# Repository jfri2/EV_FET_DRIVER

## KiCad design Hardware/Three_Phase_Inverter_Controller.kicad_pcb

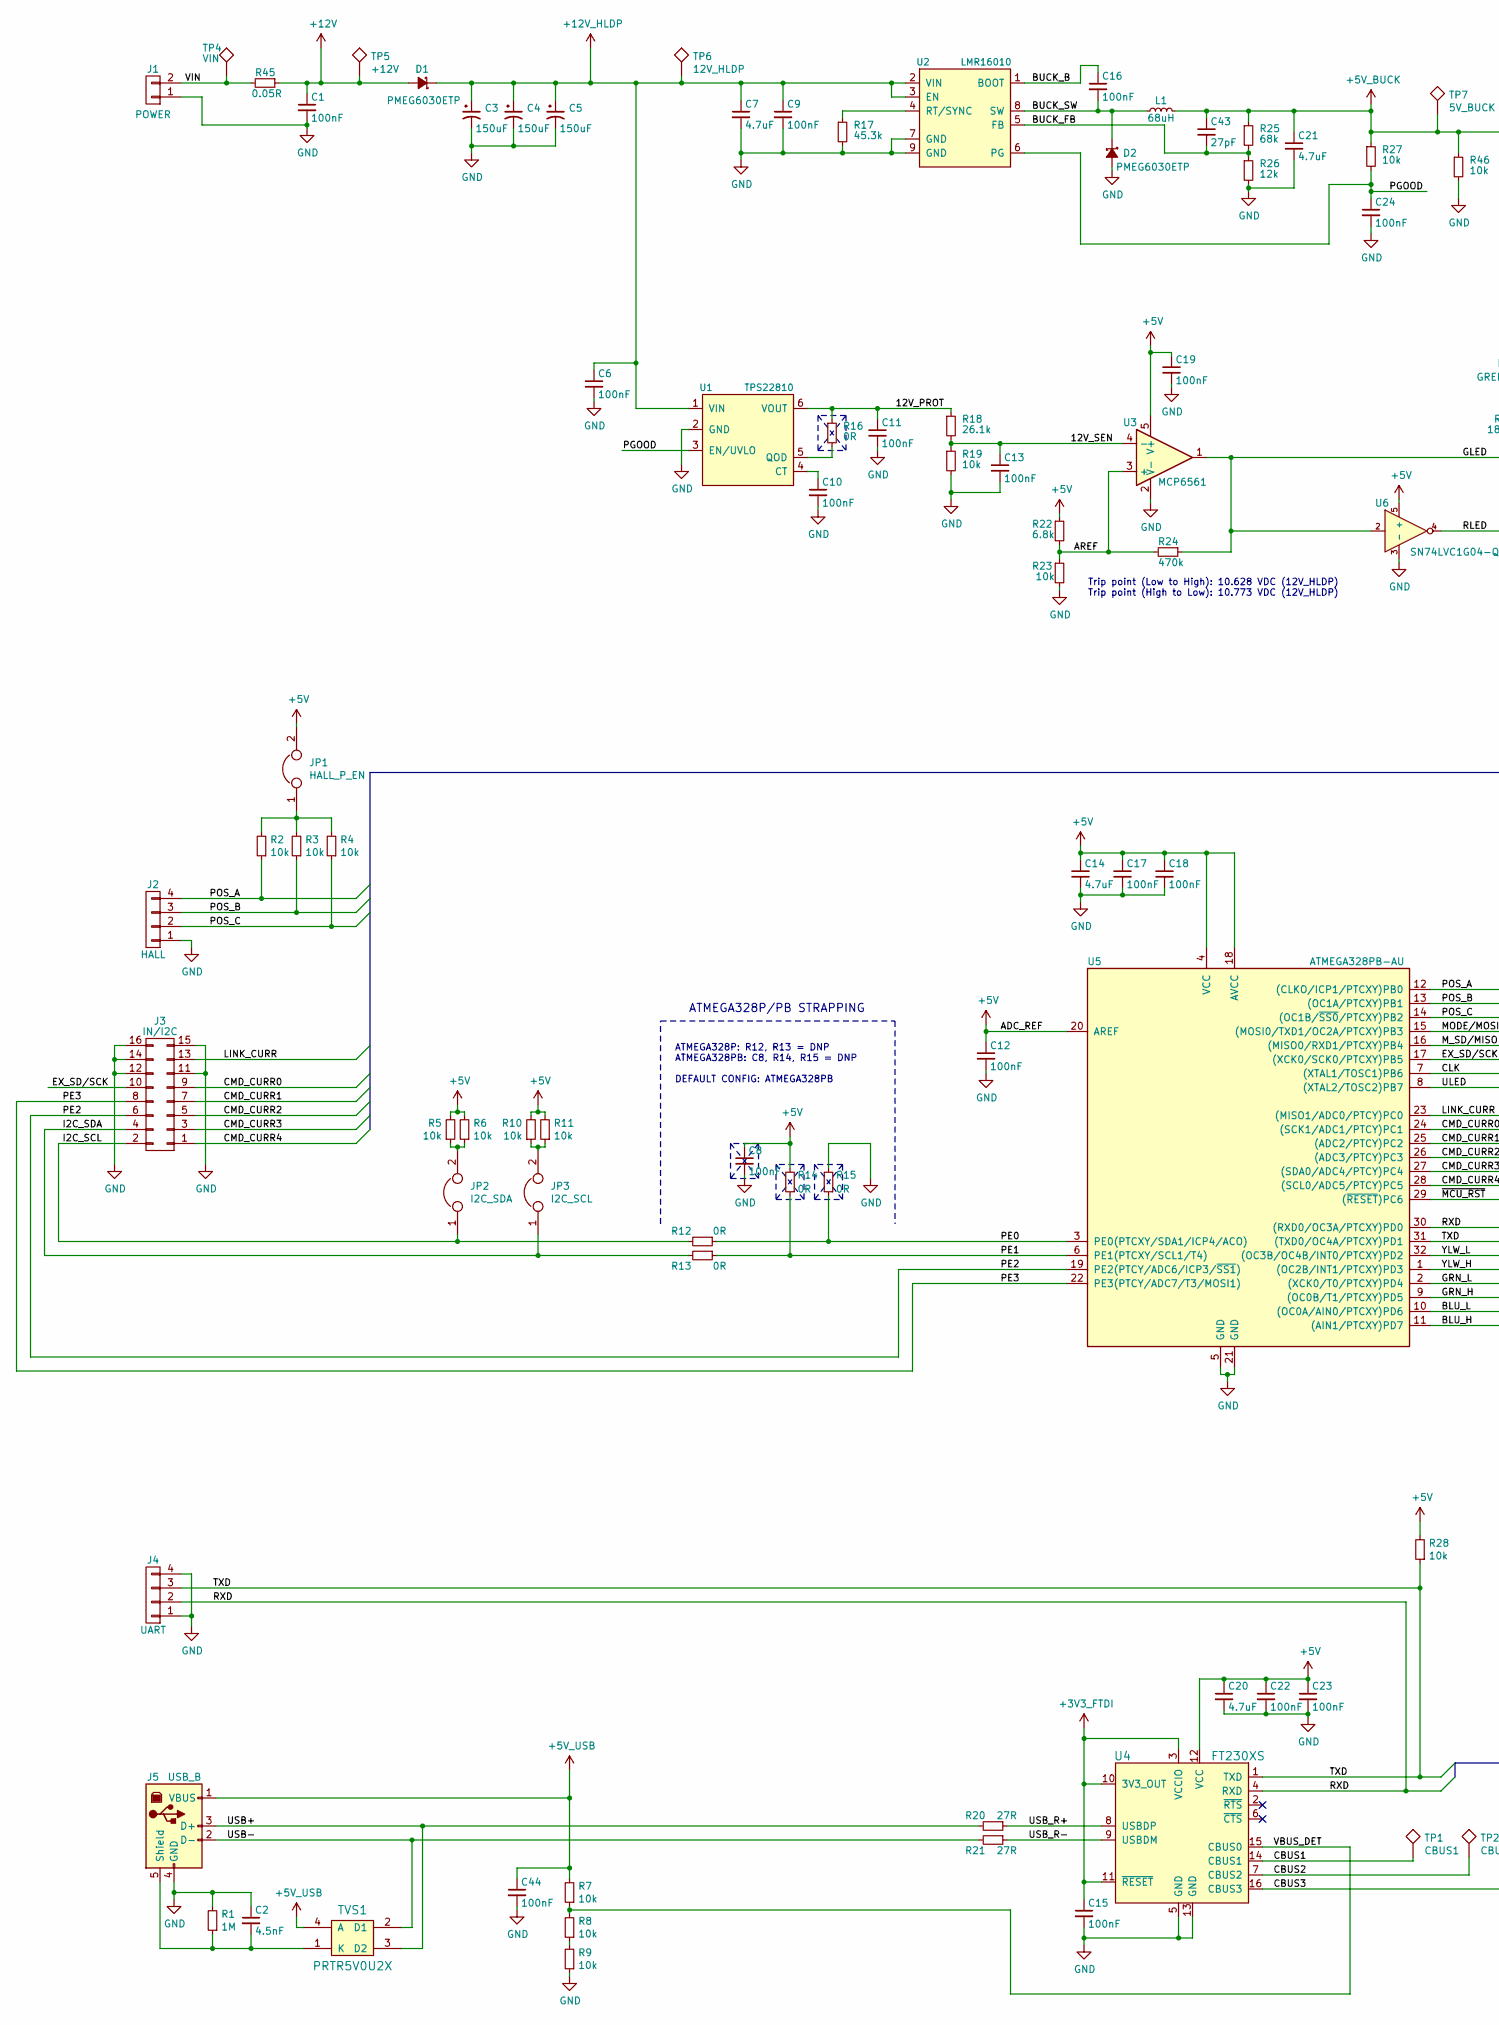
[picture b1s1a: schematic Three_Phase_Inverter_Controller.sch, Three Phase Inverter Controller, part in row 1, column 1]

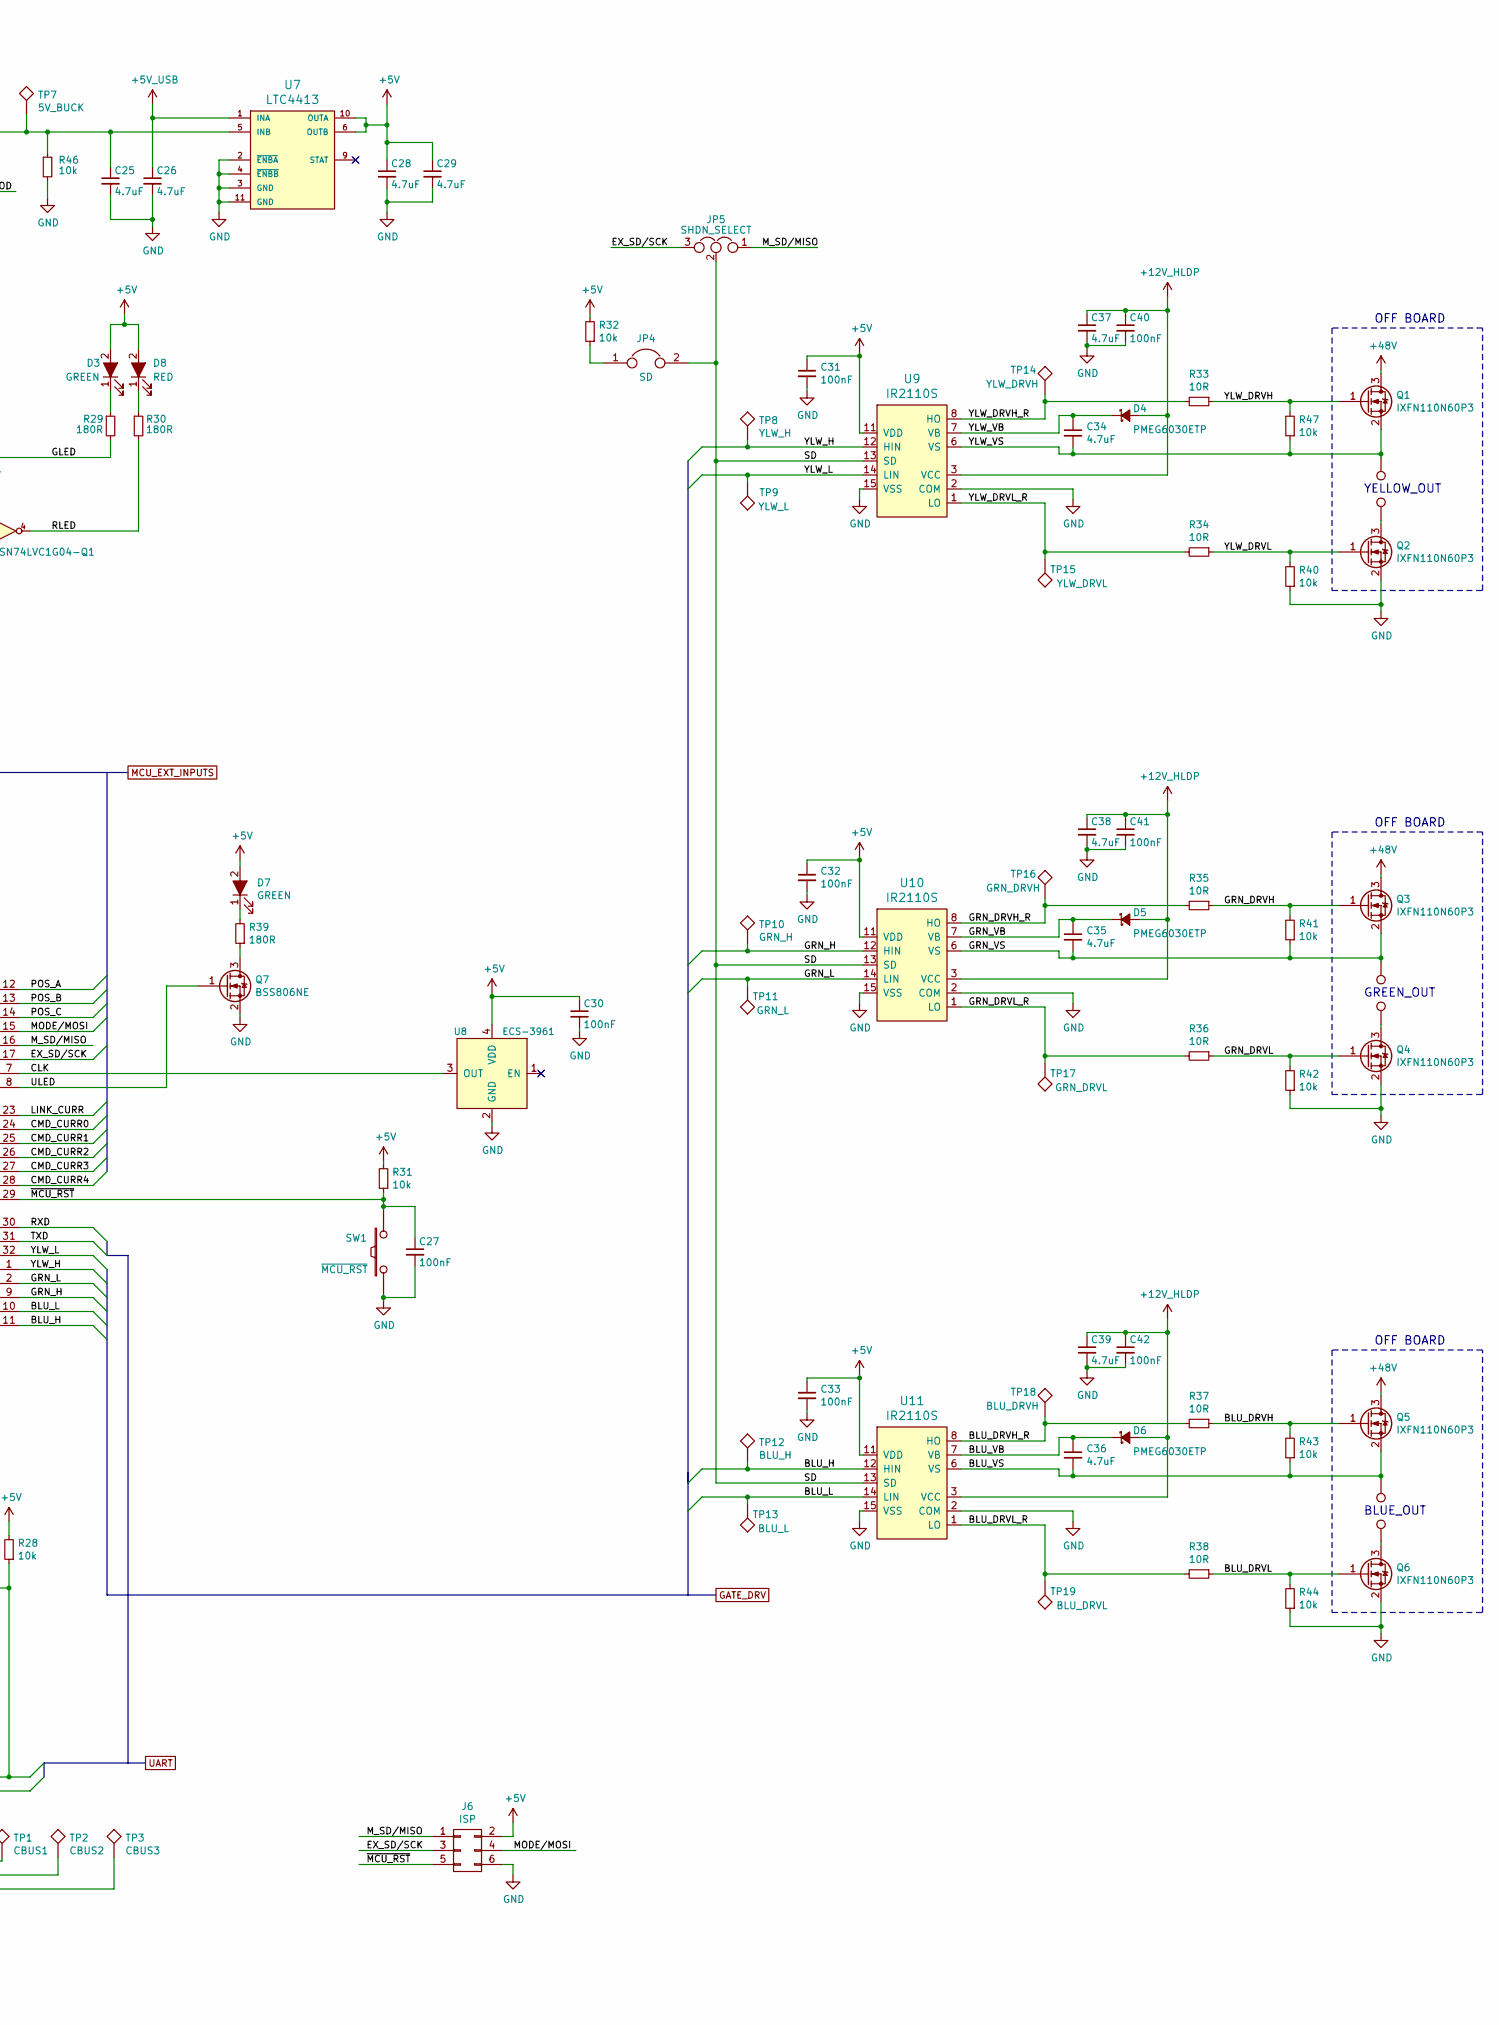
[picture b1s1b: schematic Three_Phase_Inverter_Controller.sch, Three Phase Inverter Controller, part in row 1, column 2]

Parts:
AA1, AA3, AA5: OUT_1_H
AA2, AA4, AA6: OUT_1_L
C1, C6, C8, C9, C10, C11, C12, C13, C15, C16, C17, C18, C19, C22, C23, C24, C27, C30, C31, C32, C33, C40, C41, C42, C44: 100nF; C_0603
C2: 4.5nF; C_0603
C3, C4, C5: 150uF; CP_Elec_10x10.5
C7, C14, C20, C21, C25, C26, C28, C29, C34, C35, C36, C37, C38, C39: 4.7uF; C_1206
C43: 27pF; C_0603
D1, D2, D4, D5, D6: PMEG6030ETP; SOD-128
D3, D7: GREEN; LED_1206
D8: RED; LED_1206
J1: POWER; TerminalBlock_Pheonix_MPT-2.54mm_2pol
J2: HALL; TerminalBlock_Pheonix_MPT-2.54mm_4pol
J3: IN/I2C; Pin_Header_Angled_2x08_Pitch2.54mm
J4: UART; Pin_Header_Angled_1x04_Pitch2.54mm
J5: USB_B; USB-B_62910416121
J6: ISP; Pin_Header_Straight_2x03_Pitch2.54mm
JP1: HALL_P_EN; Pin_Header_Straight_2x01_Pitch2.00mm
JP2: I2C_SDA; Pin_Header_Straight_2x01_Pitch2.00mm
JP3: I2C_SCL; Pin_Header_Straight_2x01_Pitch2.00mm
JP4: SD; Pin_Header_Straight_2x01_Pitch2.00mm
JP5: SHDN_SELECT; Pin_Header_Straight_1x03_Pitch2.54mm
L1: 68uH; BOURNS_SDR0604
Q1, Q2, Q3, Q4, Q5, Q6: IXFN110N60P3; M4_SCREW_OFFSET_9.5_16ths
Q7: BSS806NE; SOT-23
R1: 1M; R_0603
R2, R3, R4, R5, R6, R7, R8, R9, R10, R11, R19, R23, R27, R28, R31, R32, R40, R41, R42, R43, R44, R46, R47: 10k; R_0603
R12, R13, R14, R15, R16: 0R; R_0603
R17: 45.3k; R_0603
R18: 26.1k; R_0603
R20, R21: 27R; R_0603
R22: 6.8k; R_0603
R24: 470k; R_0603
R25: 68k; R_0603
R26: 12k; R_0603
R29, R30: 180R; R_0805
R33, R34, R35, R36, R37, R38: 10R; R_0805
R39: 180R; R_0603
R45: 0.05R; R_1206
SW1: ~MCU_RST; SW_SPST_TL3342
TP1: CBUS1; Test_Point_Keystone_5019_Minature
TP2: CBUS2; Test_Point_Keystone_5019_Minature
TP3: CBUS3; Test_Point_Keystone_5019_Minature
TP4: VIN; Test_Point_Keystone_5019_Minature
TP5: +12V; Test_Point_Keystone_5019_Minature
TP6: 12V_HLDP; Test_Point_Keystone_5019_Minature
TP7: 5V_BUCK; Test_Point_Keystone_5019_Minature
TP8: YLW_H; Test_Point_Keystone_5019_Minature
TP9: YLW_L; Test_Point_Keystone_5019_Minature
TP10: GRN_H; Test_Point_Keystone_5019_Minature
TP11: GRN_L; Test_Point_Keystone_5019_Minature
TP12: BLU_H; Test_Point_Keystone_5019_Minature
TP13: BLU_L; Test_Point_Keystone_5019_Minature
TP14: YLW_DRVH; Test_Point_Keystone_5019_Minature
TP15: YLW_DRVL; Test_Point_Keystone_5019_Minature
TP16: GRN_DRVH; Test_Point_Keystone_5019_Minature
TP17: GRN_DRVL; Test_Point_Keystone_5019_Minature
TP18: BLU_DRVH; Test_Point_Keystone_5019_Minature
TP19: BLU_DRVL; Test_Point_Keystone_5019_Minature
TVS1: PRTR5V0U2X; SOT-143
U1: TPS22810; SOT-23-6
U2: LMR16010; SOIC-8-1EP_3.9x4.9mm_Pitch1.27mm
U3: MCP6561; SOT-23-5
U4: FT230XS; SSOP-16_3.9x4.9mm_Pitch0.635mm
U5: ATMEGA328PB-AU; TQFP-32_7x7mm_Pitch0.8mm
U6: SN74LVC1G04-Q1; SOT-23-5
U7: LTC4413; DFN-10-1EP_3x3mm_Pitch0.5mm
U8: ECS-3961; Oscillator_SMD_EuroQuartz_XO53-4pin_5.0x3.2mm
U9, U10, U11: IR2110S; SOIC-16W_7.5x10.3mm_Pitch1.27mm

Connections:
+3V3_FTDI: C15.1, U4.3 (VCCIO), U4.10 (3V3_OUT), U4.11 (~RESET)
+5V: C8.1, C12.1, C14.1, C17.1, C18.1, C19.1, C20.1, C22.1, C23.1, C28.1, C29.1, C30.1, C31.1, C32.1, C33.1, D3.2 (A), D7.2 (A), D8.2 (A), J6.2, JP1.2, R5.2, R6.2, R10.2, R11.2, R14.2, R22.1, R28.2, R31.2, R32.2, U3.5 (V+), U4.12 (VCC), U5.4 (VCC), U5.18 (AVCC), U5.20 (AREF), U6.5 (+), U7.6 (OUTB), U7.10 (OUTA), U8.4 (VDD), U9.11 (VDD), U10.11 (VDD), U11.11 (VDD)
+5V_BUCK: C21.1, C25.1, C43.1, L1.2, R25.1, R27.1, R46.1, TP7.1, U7.5 (INB)
+5V_USB: C26.1, C44.1, J5.1 (VBUS), R7.2, TVS1.4 (A), U7.1 (INA)
+12V: C1.1, D1.2 (A), R45.1, TP5.1
+12V_HLDP: C3.1, C4.1, C5.1, C6.1, C7.1, C9.1, C37.1, C38.1, C39.1, C40.1, C41.1, C42.1, D1.1 (K), D4.2 (A), D5.2 (A), D6.2 (A), TP6.1, U1.1 (VIN), U2.2 (VIN), U2.3 (EN), U9.3 (VCC), U10.3 (VCC), U11.3 (VCC)
/12V_PROT: C11.1, R16.1, R18.1, U1.6 (VOUT)
/12V_SEN: C13.1, R18.2, R19.1, U3.4 (-)
/AREF: R22.2, R23.1, R24.2, U3.3 (+)
/BLU_DRVH: Q5.1 (G), R37.1, R43.2
/BLU_DRVH_R: R37.2, TP18.1, U11.8 (HO)
/BLU_DRVL: Q6.1 (G), R38.1, R44.2
/BLU_DRVL_R: R38.2, TP19.1, U11.1 (LO)
/BLU_H: TP12.1, U5.11 ((AIN1/PTCXY)PD7), U11.12 (HIN)
/BLU_L: TP13.1, U5.10 ((OC0A/AIN0/PTCXY)PD6), U11.14 (LIN)
/BLU_VB: C36.1, D6.1 (K), U11.7 (VB)
/BLU_VS: AA5.1, C36.2, Q5.2 (S), R43.1, U11.6 (VS)
/BUCK_B: C16.1, U2.1 (BOOT)
/BUCK_FB: C43.2, R25.2, R26.1, U2.5 (FB)
/BUCK_SW: C16.2, D2.1 (K), L1.1, U2.8 (SW)
/CBUS1: TP1.1, U4.14 (CBUS1)
/CBUS2: TP2.1, U4.7 (CBUS2)
/CBUS3: TP3.1, U4.16 (CBUS3)
/CLK: U5.7 ((XTAL1/TOSC1)PB6), U8.3 (OUT)
/CMD_CURR0: J3.9, U5.24 ((SCK1/ADC1/PTCY)PC1)
/CMD_CURR1: J3.7, U5.25 ((ADC2/PTCY)PC2)
/CMD_CURR2: J3.5, U5.26 ((ADC3/PTCY)PC3)
/CMD_CURR3: J3.3, U5.27 ((SDA0/ADC4/PTCY)PC4)
/CMD_CURR4: J3.1, U5.28 ((SCL0/ADC5/PTCY)PC5)
/EX_SD/SCK: J3.10, J6.3, JP5.3, U5.17 ((XCK0/SCK0/PTCXY)PB5)
/GLED: R24.1, R29.2, U3.1, U6.2
/GRN_DRVH: Q3.1 (G), R35.1, R41.2
/GRN_DRVH_R: R35.2, TP16.1, U10.8 (HO)
/GRN_DRVL: Q4.1 (G), R36.1, R42.2
/GRN_DRVL_R: R36.2, TP17.1, U10.1 (LO)
/GRN_H: TP10.1, U5.9 ((OC0B/T1/PTCXY)PD5), U10.12 (HIN)
/GRN_L: TP11.1, U5.2 ((XCK0/T0/PTCXY)PD4), U10.14 (LIN)
/GRN_VB: C35.1, D5.1 (K), U10.7 (VB)
/GRN_VS: AA3.1, C35.2, Q3.2 (S), R41.1, U10.6 (VS)
/I2C_SCL: J3.2, JP2.1, R12.2
/I2C_SDA: J3.4, JP3.1, R13.2
/LINK_CURR: J3.13, U5.23 ((MISO1/ADC0/PTCY)PC0)
/MODE/MOSI: J6.4, U5.15 ((MOSI0/TXD1/OC2A/PTCXY)PB3)
/M_SD/MISO: J6.1, JP5.1, U5.16 ((MISO0/RXD1/PTCXY)PB4)
/PE0: R12.1, R15.1, U5.3 (PE0(PTCXY/SDA1/ICP4/ACO))
/PE1: R13.1, R14.1, U5.6 (PE1(PTCXY/SCL1/T4))
/PE2: J3.6, U5.19 (PE2(PTCY/ADC6/ICP3/~SS1~))
/PE3: J3.8, U5.22 (PE3(PTCY/ADC7/T3/MOSI1))
/PGOOD: C24.1, R27.2, U1.3 (EN/UVLO), U2.6 (PG)
/POS_A: J2.4, R2.1, U5.12 ((CLKO/ICP1/PTCXY)PB0)
/POS_B: J2.3, R3.1, U5.13 ((OC1A/PTCXY)PB1)
/POS_C: J2.2, R4.1, U5.14 ((OC1B/~SS0~/PTCXY)PB2)
/RLED: R30.2, U6.4
/RXD: J4.2, U4.4 (RXD), U5.30 ((RXD0/OC3A/PTCXY)PD0)
/SD: JP4.2, JP5.2, U9.13 (SD), U10.13 (SD), U11.13 (SD)
/TXD: J4.3, R28.1, U4.1 (TXD), U5.31 ((TXD0/OC4A/PTCXY)PD1)
/ULED: Q7.1 (G), U5.8 ((XTAL2/TOSC2)PB7)
/USB+: J5.3 (D+), R20.2, TVS1.3 (D2)
/USB-: J5.2 (D-), R21.2, TVS1.2 (D1)
/USB_R+: R20.1, U4.8 (USBDP)
/USB_R-: R21.1, U4.9 (USBDM)
/VBUS_DET: R7.1, R8.2, U4.15 (CBUS0)
/VIN: J1.2, R45.2, TP4.1
/YLW_DRVH: Q1.1 (G), R33.1, R47.2
/YLW_DRVH_R: R33.2, TP14.1, U9.8 (HO)
/YLW_DRVL: Q2.1 (G), R34.1, R40.2
/YLW_DRVL_R: R34.2, TP15.1, U9.1 (LO)
/YLW_H: TP8.1, U5.1 ((OC2B/INT1/PTCXY)PD3), U9.12 (HIN)
/YLW_L: TP9.1, U5.32 ((OC3B/OC4B/INT0/PTCXY)PD2), U9.14 (LIN)
/YLW_VB: C34.1, D4.1 (K), U9.7 (VB)
/YLW_VS: AA1.1, C34.2, Q1.2 (S), R47.1, U9.6 (VS)
/~MCU_RST: C27.1, J6.5, R31.1, SW1.2, U5.29 ((~RESET~)PC6)
GND: C1.2, C2.1, C3.2, C4.2, C5.2, C6.2, C7.2, C8.2, C9.2, C10.2, C11.2, C12.2, C13.2, C14.2, C15.2, C17.2, C18.2, C19.2, C20.2, C21.2, C22.2, C23.2, C24.2, C25.2, C26.2, C27.2, C28.2, C29.2, C30.2, C31.2, C32.2, C33.2, C37.2, C38.2, C39.2, C40.2, C41.2, C42.2, C44.2, D2.2 (A), J1.1, J2.1, J3.11, J3.12, J3.14, J3.15, J3.16, J4.1, J4.4, J5.4 (GND), J6.6, Q2.2 (S), Q4.2 (S), Q6.2 (S), Q7.2 (S), R1.2, R9.1, R15.2, R17.2, R19.2, R23.2, R26.2, R40.1, R42.1, R44.1, R46.2, SW1.1, U1.2 (GND), U2.7 (GND), U2.9 (GND), U3.2 (V-), U4.5 (GND), U4.13 (GND), U5.5 (GND), U5.21 (GND), U6.3 (-), U7.2 (~ENBA), U7.3 (GND), U7.4 (~ENBB), U7.11 (GND), U8.2 (GND), U9.2 (COM), U9.15 (VSS), U10.2 (COM), U10.15 (VSS), U11.2 (COM), U11.15 (VSS)
unnamed: AA2.1, Q2.3 (D)
unnamed: AA4.1, Q4.3 (D)
unnamed: AA6.1, Q6.3 (D)
unnamed: C2.2, J5.5 (Shield), R1.1, TVS1.1 (K)
unnamed: C10.1, U1.4 (CT)
unnamed: D3.1 (K), R29.1
unnamed: D7.1 (K), R39.2
unnamed: D8.1 (K), R30.1
unnamed: JP1.1, R2.2, R3.2, R4.2
unnamed: JP2.2, R5.1, R6.1
unnamed: JP3.2, R10.1, R11.1
unnamed: JP4.1, R32.1
unnamed: Q7.3 (D), R39.1
unnamed: R8.1, R9.2
unnamed: R16.2, U1.5 (QOD)
unnamed: R17.1, U2.4 (RT/SYNC)

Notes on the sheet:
OFF BOARD
YELLOW_OUT
GREEN_OUT
BLUE_OUT
ATMEGA328P/PB STRAPPING
ATMEGA328P: R12, R13 = DNP ATMEGA328PB: C8, R14, R15 = DNP DEFAULT CONFIG: ATMEGA328PB
Trip point (Low to High): 10.628 VDC (12V_HLDP) Trip point (High to Low): 10.773 VDC (12V_HLDP)

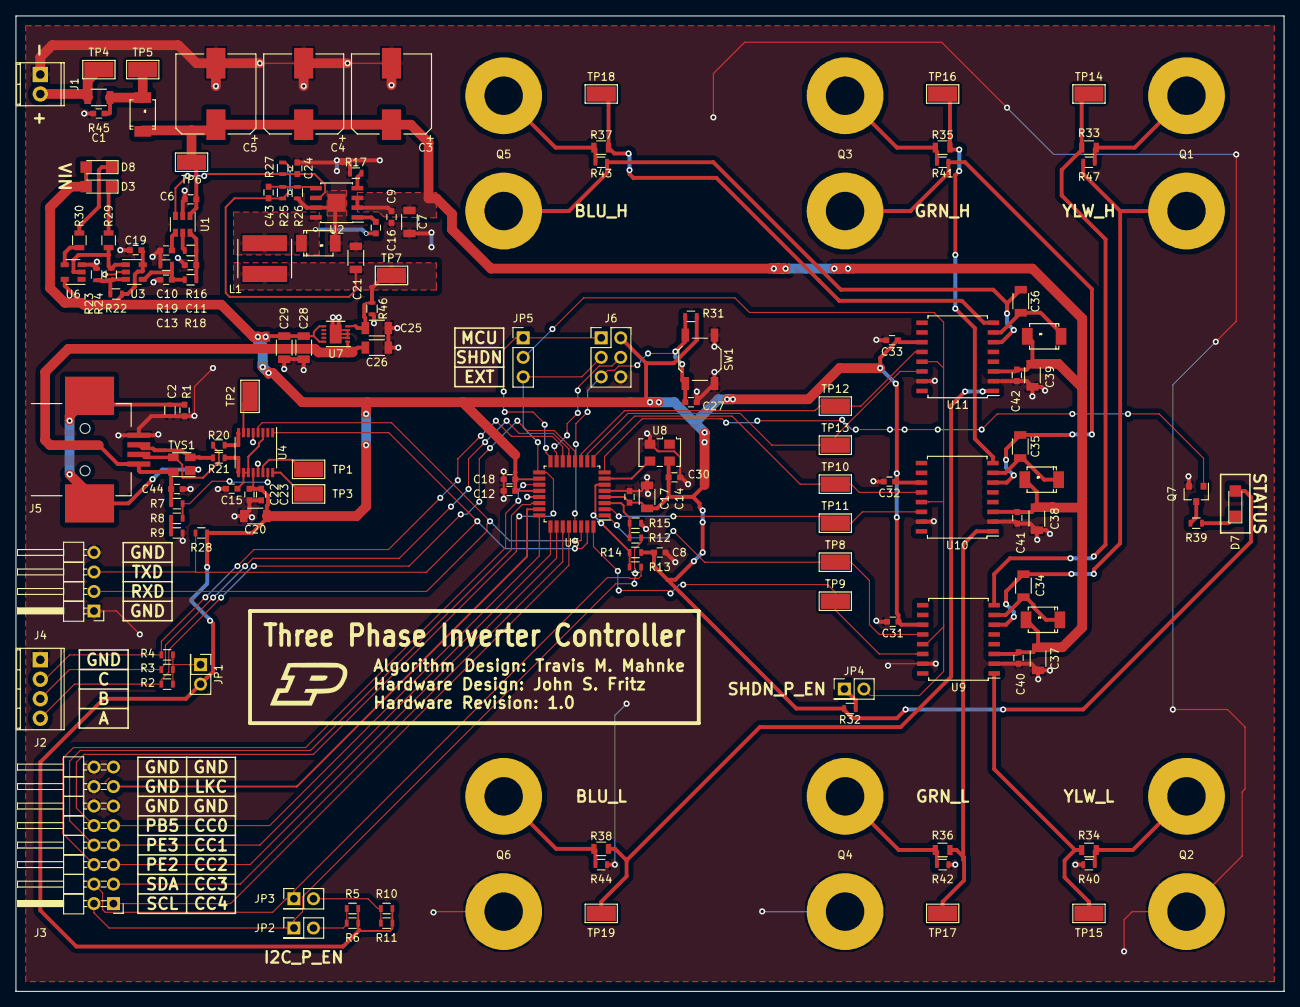
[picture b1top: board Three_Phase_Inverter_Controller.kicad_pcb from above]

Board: 2 copper layers, 165.1 x 127.0 mm, 150 parts (0 on the bottom side), 86 nets.

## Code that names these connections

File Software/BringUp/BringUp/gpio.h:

#include <stdbool.h>

// Types
typedef enum
{
    input = 0,
    output = 1
} IO;

typedef enum
{
    low = 0,
    high = 1
} LEVEL;

typedef enum
{
    high_z = 0,
    pullup = 1
} INPUT_Z;

typedef struct
{
    uint8_t pin;
    uint8_t *port;
    uint8_t *input_reg;
    uint8_t *ddr;
    IO io_type;
    LEVEL level;            // outputs only
    INPUT_Z impedance;      // inputs only    
} GPIO_PIN;

// Functions
void gpio_init_pin(GPIO_PIN pin);
void gpio_set_pin(GPIO_PIN gpio_pin);
void gpio_clear_pin(GPIO_PIN gpio_pin);
void gpio_toggle_pin(GPIO_PIN gpio_pin);
bool gpio_get_pin(GPIO_PIN gpio_pin);

// Global Variable Declarations
extern GPIO_PIN POS_A_PIN;
extern GPIO_PIN POS_B_PIN;
extern GPIO_PIN POS_C_PIN;
extern GPIO_PIN MODE_PIN;
extern GPIO_PIN INV_MCU_SHDN_PIN;
extern GPIO_PIN INV_EXT_SHDN_PIN;
extern GPIO_PIN LED_PIN;
extern GPIO_PIN LINK_CUR_PIN;
extern GPIO_PIN CMD_CURR_0_PIN;
extern GPIO_PIN CMD_CURR_1_PIN;
extern GPIO_PIN CMD_CURR_2_PIN;
extern GPIO_PIN CMD_CURR_3_PIN;
extern GPIO_PIN CMD_CURR_4_PIN;
extern GPIO_PIN YLW_L_PIN;
extern GPIO_PIN YLW_H_PIN;
extern GPIO_PIN GRN_L_PIN;
extern GPIO_PIN GRN_H_PIN;
extern GPIO_PIN BLU_L_PIN;
extern GPIO_PIN BLU_H_PIN;

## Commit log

2017-04-03 :boom::camel: Added .gitattributes & .gitignore files
2017-04-05 Added datasheets. Selected oscillator
2017-04-06 Added wire
2017-04-09 Hardware architecture done. Starting schematic drafting
2017-04-09 renamed project. Added more datasheets
2017-04-13 Updated schematic
2017-04-13 Regenerated schematic PDF
2017-04-13 Added Diode OR to Power Supply
2017-04-13 Annotated schematic
2017-04-18 Pre-release v0.3 Schematic
2017-04-21 Updated BOM & finished SCH
2017-04-21 Regenerate schematic PDF
2017-04-22 Assigned footrpints for most components, tweaked BOM
2017-04-26 Changed connector, started layout, save before reloading new netlist
2017-04-26 More layout done
2017-04-26 Generate dimension check PDF
2017-04-26 Regenerate sch PDF
2017-04-26 Updated BOM?
2017-04-28 Did stuff
2017-05-03 Started layout. Minor adjustments to schematic to make layout easier.
2017-05-03 More routing and component placement complete
2017-05-04 Add new 3D models/Routed more
2017-05-10 Finished initial component placement
2017-05-11 did more routing
2017-05-12 Finished initial board layout
2017-05-15 Finished PCB, changed routing, regenerated schematic, generated gerbers
    Put EXT_SHDN line in instead of ULED to external connector, changed
    routing to reflect that. Added finishing touches to PCB silkscreen.
2017-05-29 Started board bring up

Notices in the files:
Hardware/Three_Phase_Inverter_Controller.kicad_pcb:
CC0
